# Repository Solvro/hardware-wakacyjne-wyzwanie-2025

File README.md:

# 🔧 Wakacyjne Wyzwanie 2025 – Od zera do Hardware Developera

> Realizowane w ramach Strategicznego Koła Naukowego **Solvro** przy Politechnice Wrocławskiej  

## 📌 O kursie

Ścieżka **Hardware** to część interdyscyplinarnego projektu edukacyjnego _Wakacyjne Wyzwanie Solvro 2025_, który ma na celu wprowadzenie studentów w świat elektroniki i jej programowania.

Kurs został zaprojektowany z myślą o osobach, które chcą wyjść poza świat czysto cyfrowy i rozpocząć pracę z realnym, fizycznym sprzętem. Zajęcia obejmują zarówno część teoretyczną, jak i praktyczny projekt wykonany zespołowo.

---

## 📚 Program kursu 

🌐 __Zdalnie:__

**1.** 🔧: *Podstawowe elementy analogowe układów elektronicznych i ich wykorzystanie*  

**2.** 💡: *Podstawowe elementy cyfrowych układów elektronicznych i ich wykorzystanie*  

**3.**
- ⚙️: *Budowanie schematu i uproszczenie z mikrokontrolerami*  
  - Arduino Uno R3 — podstawy działania  
  - rola mikrokontrolera  
  - czemu przycisk idzie między GND a wejście z pull-upem i co to w ogóle znaczy?  
  - wejścia/wyjścia, PWM, ADC  
  - gotowy programator atmega16u4 – jak to działa?  

- 🧪: *Prezentacja sprzętu pomiarowego i warsztatowego*  

**4.** 🧰 *Budowa i symulacja układu prototypowego w środowisku Tinkercad*  

**5.** 🖋️ *Rysowanie schematów i projektowanie płytek PCB układów elektronicznych w KiCadzie*  

**6.** 🖨️ *Druk 3D — podstawy modelowania i przygotowania do druku*  

👨‍🔧 __Stacjonarnie:__

**7.** 🔩 *Montaż prototypowego układu projektu*  

**8.** 💾 *Zaprogramowanie elektronicznego układu prototypowego*  

---

## 👨‍🏫 Opieka merytoryczna

- **Koordynator kursu**: Michał Bocian  
  - Przewodniczący Sekcji Hardware, SKN Solvro  
- **Opiekun ekspercki (konsultacje)**: dr inż. Krzysztof Chudzik
  - Doświadczony, wieloletni inżynier branży Embedded & Hardware
  - Prowadzący kursu IoT na kierunku Informatyki Stosowanej Politechniki Wrocławskiej

---

## 📄 Certyfikacja

Uczestnicy, którzy ukończą kurs i zrealizują projekt, otrzymają **certyfikat** podpisany przez koordynatora kursu.

---

## 💡 Cele kursu

- Wprowadzenie studentów w praktyczny świat elektroniki
- Promowanie pracy przy projektach sprzętowych
- Zwiększenie świadomości inżynierskiej "od idei do prototypu"

---
## 🧠 Co będziesz umieć po kursie?

- Stworzyć proste rozwiązania sprzętowe do codziennego użytku
- Mieć świadomość dobierania komponentów i jak się z nimi obchodzić
- Zamodelować proste kształty do wydruku trójwymiarowego
- Stworzyć własne urządzenie

---

## 🤝 Partnerzy i podziękowania

Projekt realizowany dzięki wsparciu dydaktyków, członków SKN Solvro oraz Politechniki Wrocławskiej.

---

**Let's go from idea → to device.**

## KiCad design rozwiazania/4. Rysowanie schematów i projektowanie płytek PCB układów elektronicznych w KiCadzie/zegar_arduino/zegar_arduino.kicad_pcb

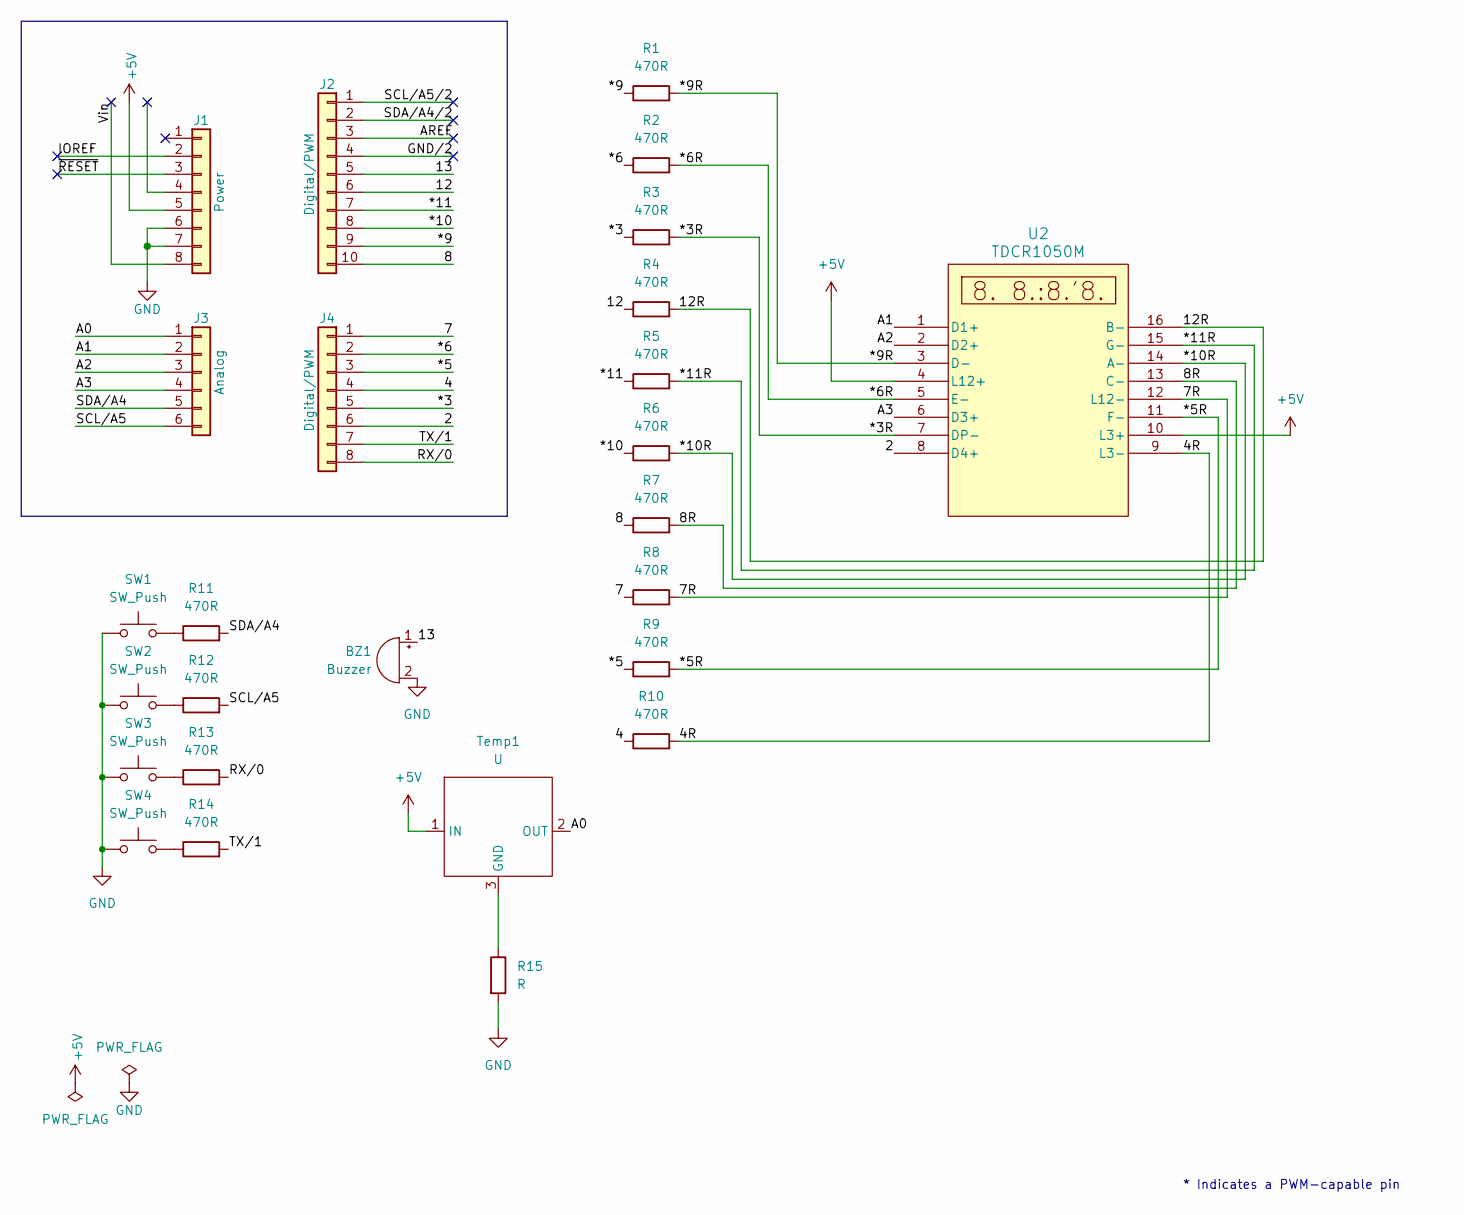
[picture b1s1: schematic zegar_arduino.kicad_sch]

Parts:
BZ1: Buzzer; Buzzer_15x7.5RM7.6
J1: Power; PinHeader_1x08_P2.54mm_Vertical
J2: Digital/PWM; PinHeader_1x10_P2.54mm_Vertical
J3: Analog; PinHeader_1x06_P2.54mm_Vertical
J4: Digital/PWM; PinHeader_1x08_P2.54mm_Vertical
R1, R2, R3, R4, R5, R6, R7, R8, R9, R10, R11, R12, R13, R14: 470R; R_1206_3216Metric_Pad1.30x1.75mm_HandSolder
R15: R; R_1206_3216Metric_Pad1.30x1.75mm_HandSolder
SW1, SW2, SW3, SW4: SW_Push; SW_PUSH_6mm
Temp1: U; TO-92
U2: TDCR1050M; TDCG1060M_VIS

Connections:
+5V: J1.5, Temp1.1 (IN), U2.4 (L12+), U2.10 (L3+)
/2: J4.6, U2.8 (D4+)
/4: J4.4, R10.1
/4R: R10.2, U2.9 (L3-)
/7: J4.1, R8.1
/7R: R8.2, U2.12 (L12-)
/8: J2.10, R7.1
/8R: R7.2, U2.13 (C-)
/12: J2.6, R4.1
/12R: R4.2, U2.16 (B-)
/13: BZ1.1 (+), J2.5
/*3: J4.5, R3.1
/*3R: R3.2, U2.7 (DP-)
/*5: J4.3, R9.1
/*5R: R9.2, U2.11 (F-)
/*6: J4.2, R2.1
/*6R: R2.2, U2.5 (E-)
/*9: J2.9, R1.1
/*9R: R1.2, U2.3 (D-)
/*10: J2.8, R6.1
/*10R: R6.2, U2.14 (A-)
/*11: J2.7, R5.1
/*11R: R5.2, U2.15 (G-)
/A0: J3.1, Temp1.2 (OUT)
/A1: J3.2, U2.1 (D1+)
/A2: J3.3, U2.2 (D2+)
/A3: J3.4, U2.6 (D3+)
/AREF: J2.3
/GND/2: J2.4
/IOREF: J1.2
/RX/0: J4.8, R13.2
/SCL/A5: J3.6, R12.2
/SCL/A5/2: J2.1
/SDA/A4: J3.5, R11.2
/SDA/A4/2: J2.2
/TX/1: J4.7, R14.2
/Vin: J1.8
/~RESET: J1.3
GND: BZ1.2 (-), J1.6, J1.7, R15.2, SW1.1, SW2.1, SW3.1, SW4.1
unnamed: R11.1, SW1.2
unnamed: R12.1, SW2.2
unnamed: R13.1, SW3.2
unnamed: R14.1, SW4.2
unnamed: R15.1, Temp1.3 (GND)

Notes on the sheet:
* Indicates a PWM-capable pin

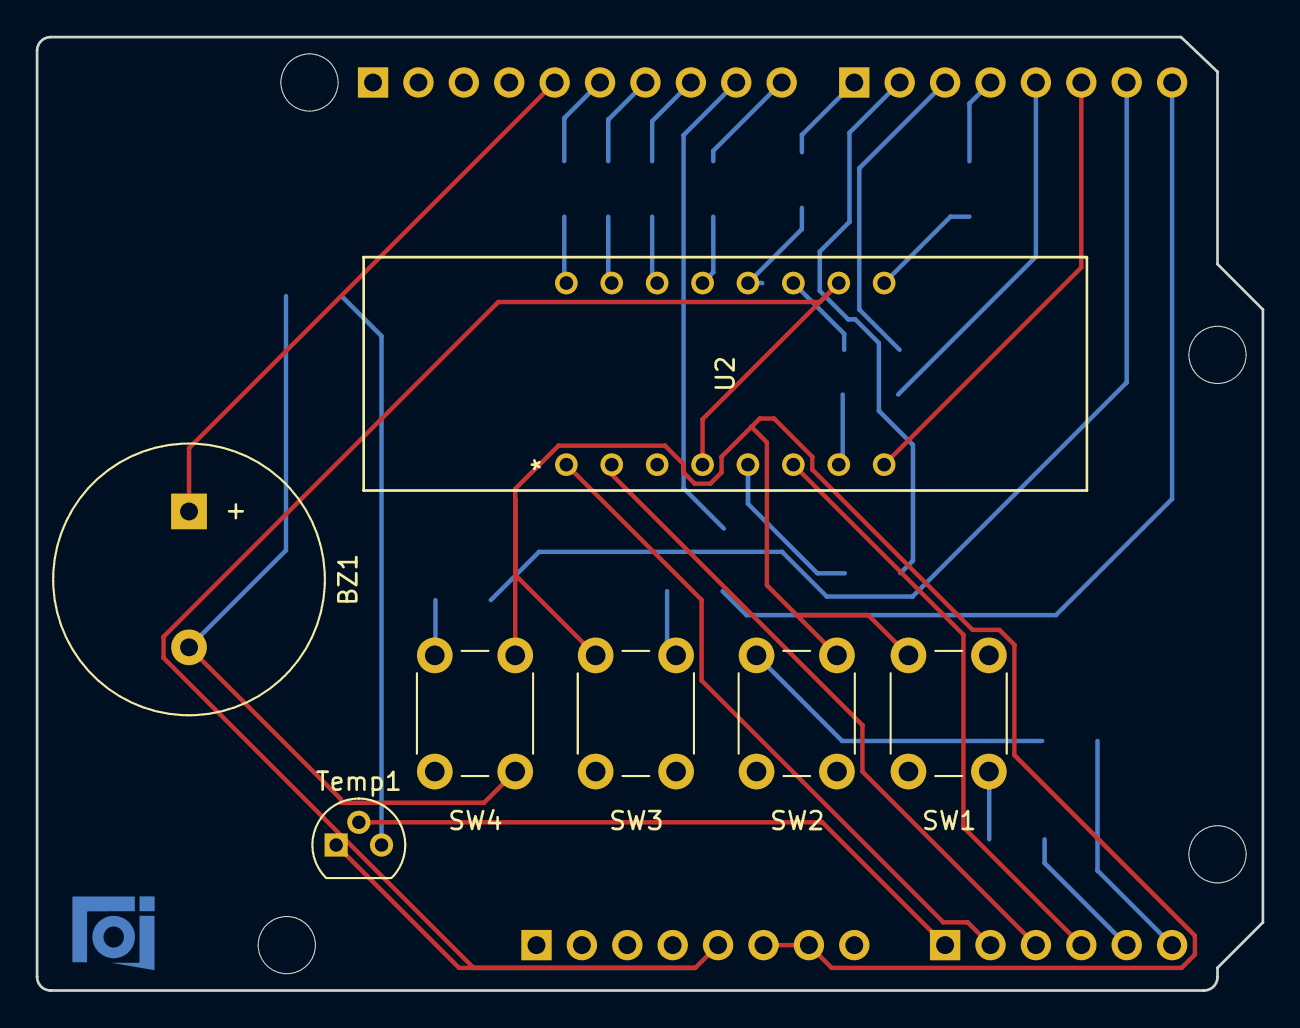
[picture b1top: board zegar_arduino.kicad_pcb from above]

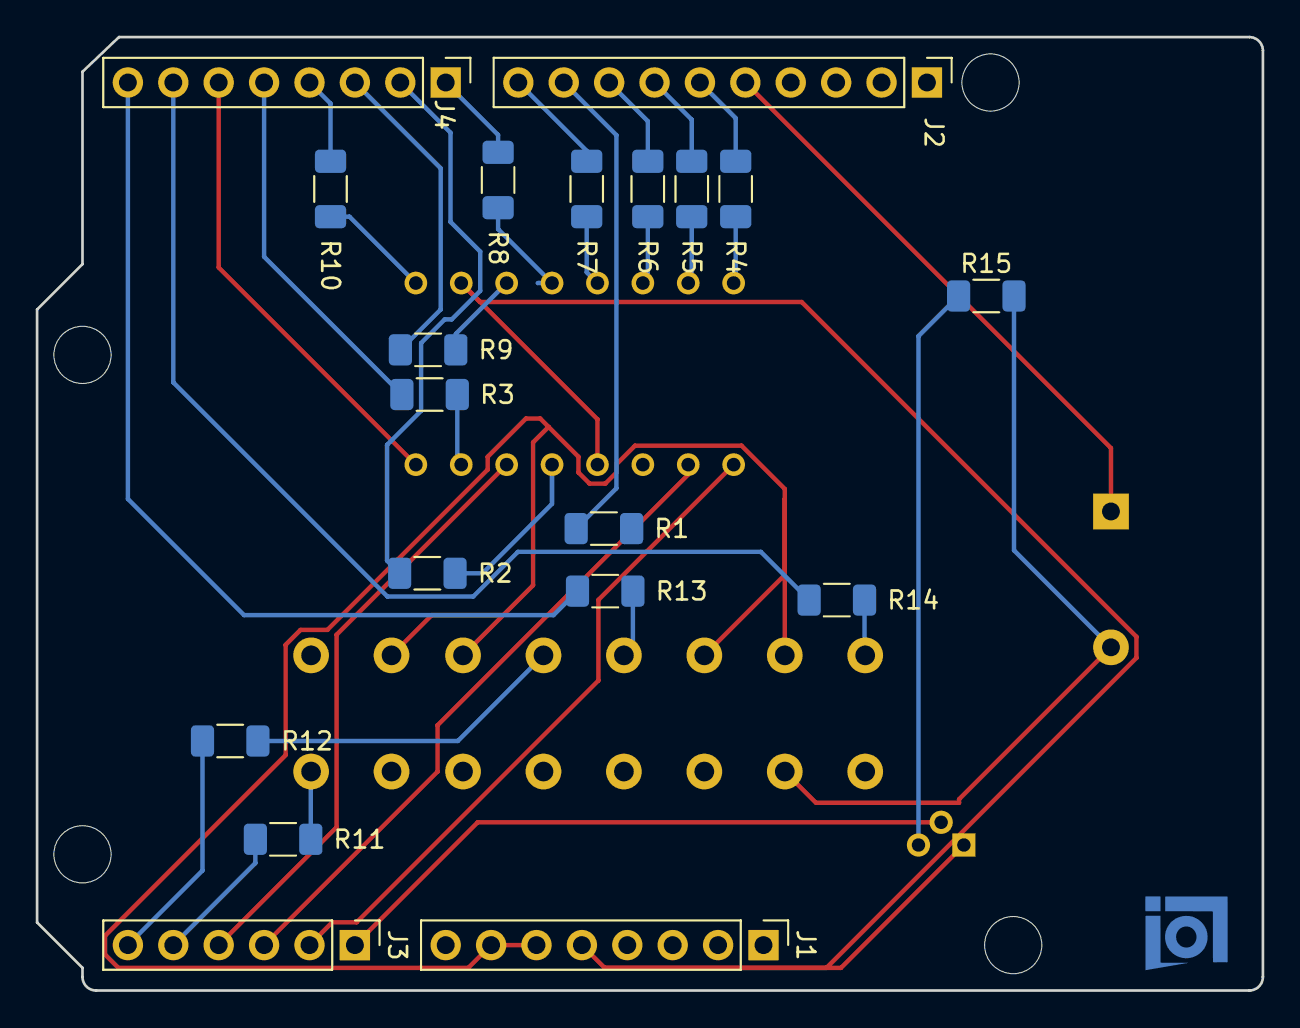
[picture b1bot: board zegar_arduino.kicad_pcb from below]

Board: 2 copper layers, 68.6 x 53.3 mm, 30 parts (19 on the bottom side), 37 nets.

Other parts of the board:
MH1, MH2, MH3, MH4: MountingHole_3.2mm

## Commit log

2025-07-14 Update README.md
    Information for Hardware course
2025-08-03 Update README.md
    completion of documentation
2025-08-08 lista 1
2025-08-08 Update readme.md
    spelling mistake
2025-08-11 lista1
2025-08-12 List 1 without 4th task
2025-08-12 List 1 add task 4
2025-08-12 Rozwiązania listy 1
2025-08-13 list 1 tasks w/o 4
2025-08-15 task 4
2025-08-16 Create rozwiązania
2025-08-18 lista 3
2025-08-19 Rozwiazania Lista 2
2025-08-19 list 2, tasks 2 and 3
2025-08-21 list 2 task 1
2025-08-26 list 2 task 2 and 3
2025-08-26 dodane rozwiazania do listy 1
2025-08-26 dodano folder dla listy 1
2025-09-06 projekty 1 i 2
2025-09-08 dodano rozwiazanie do listy 3
2025-09-09 Dodano link lista3.md
2025-09-10 dodano rozwiazanie listy 4
2025-10-04 dodalem rozwiazania do listy 2
